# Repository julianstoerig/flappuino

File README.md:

# flappuino
tiny flappy bird for arduino w/OLED

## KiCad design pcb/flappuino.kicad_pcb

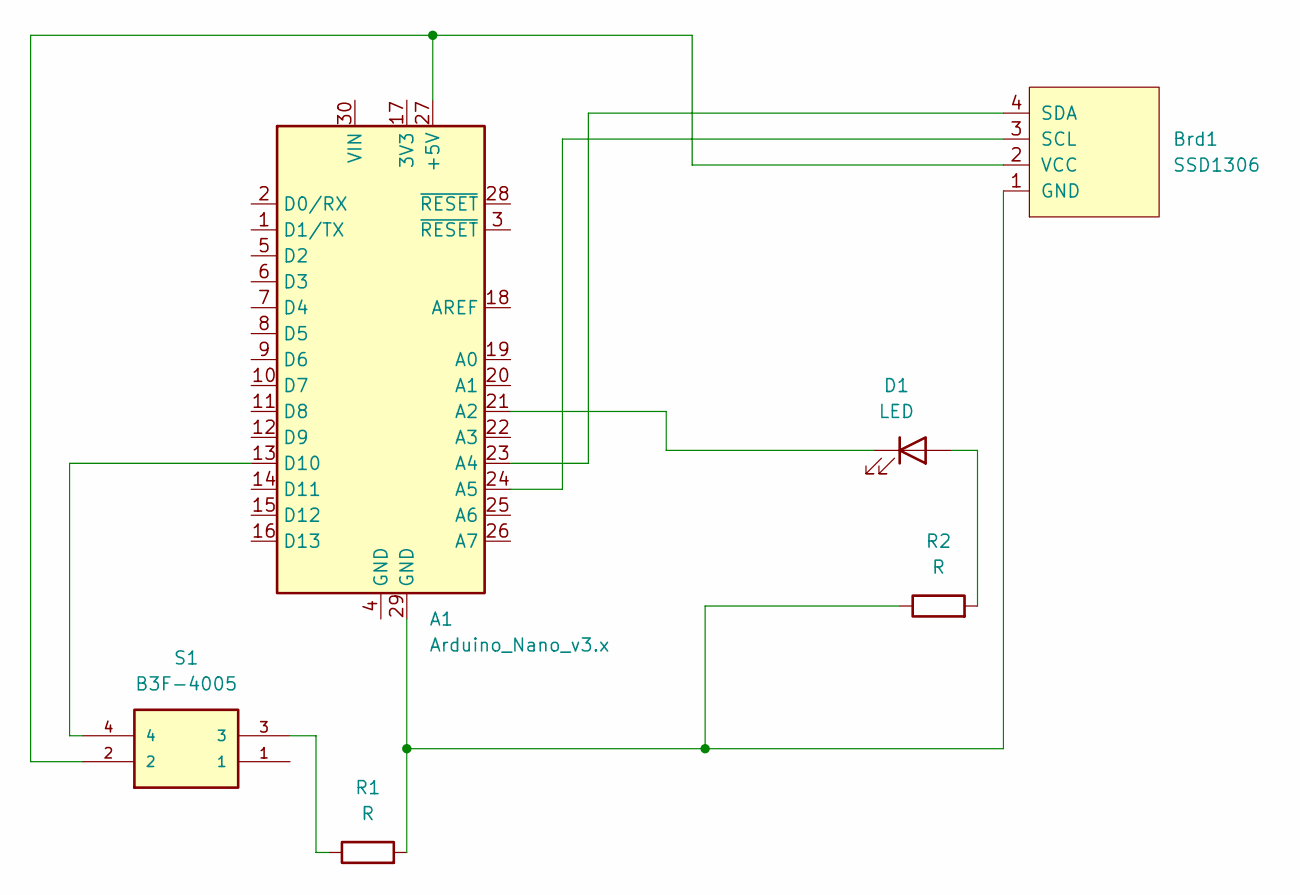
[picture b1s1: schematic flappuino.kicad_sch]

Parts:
A1: Arduino_Nano_v3.x; Arduino_Nano
Brd1: SSD1306; 128x64OLED
D1: LED; LED Universal Thruhole
R1, R2: R; Resistor Universal Thruhole
S1: B3F-4005; B3F-4055; Mouser_Part_Number 653-B3F-4005

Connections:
unnamed: A1.27 (+5V), Brd1.2 (VCC), S1.2
unnamed: A1.21 (A2), D1.1 (K)
unnamed: A1.23 (A4), Brd1.4 (SDA)
unnamed: A1.24 (A5), Brd1.3 (SCL)
unnamed: A1.13 (D10), S1.4
unnamed: A1.29 (GND), Brd1.1 (GND), R1.2, R2.1
unnamed: D1.2 (A), R2.2
unnamed: R1.1, S1.3

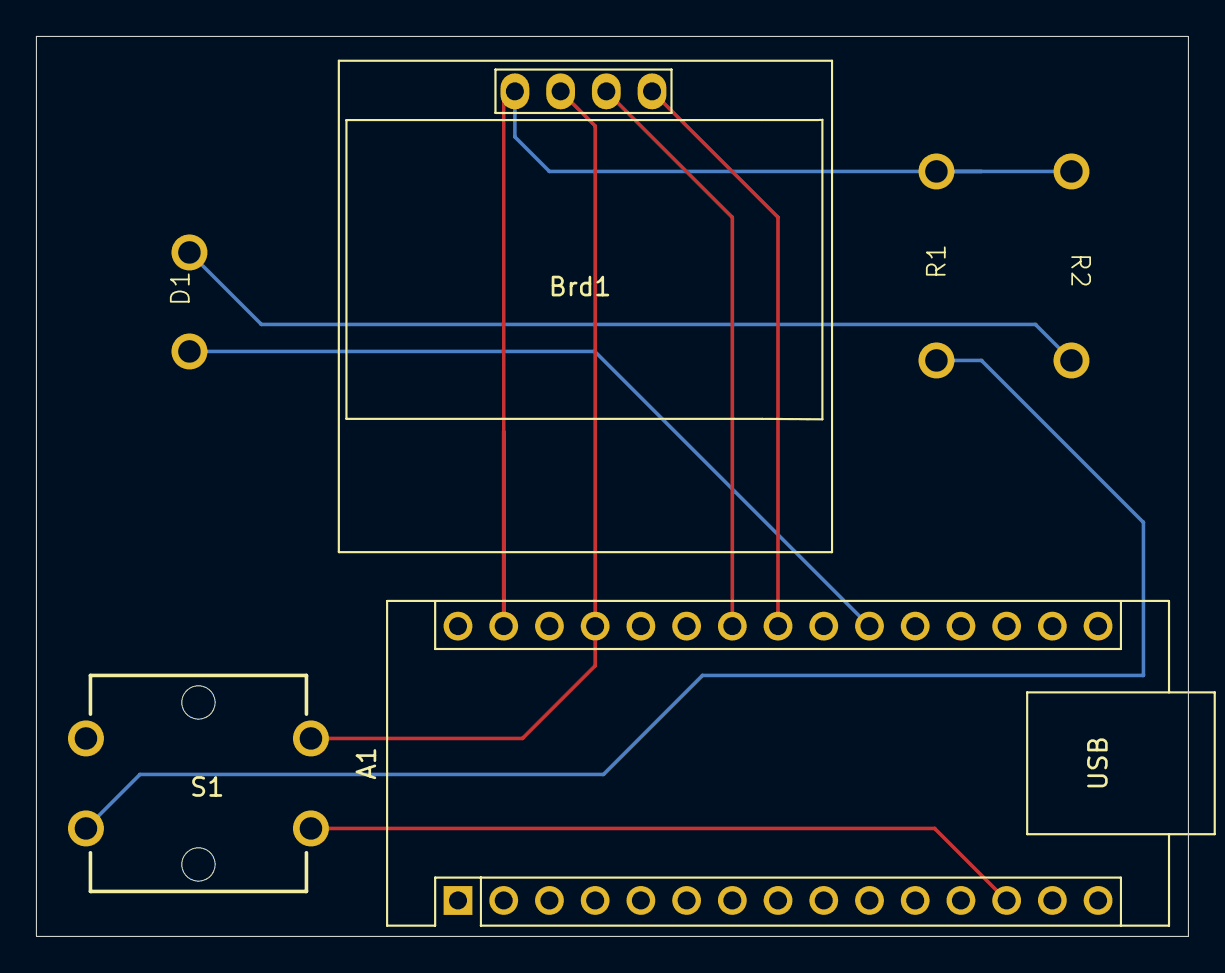
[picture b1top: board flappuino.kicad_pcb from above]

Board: 2 copper layers, 64.0 x 50.0 mm, 6 parts (0 on the bottom side), 8 nets.

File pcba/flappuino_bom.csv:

Designator,Footprint,Quantity,Value,LCSC Part #
A1,Arduino_Nano,1,Arduino_Nano_v3.x,
BRD1,128x64OLED,1,SSD1306,
D1,LED Universal Thruhole,1,LED,
"R1, R2",Resistor Universal Thruhole,2,R,
S1,B3F-4055,1,B3F-4005,

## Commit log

2025-11-11 adjust doc comments
2025-11-11 finalise ssd1306 init proc
2025-11-11 stuff
2025-11-11 remove text for size reasons
2025-11-11 next
2025-11-13 add error reporting
2025-11-13 remove unused file
2025-11-13 double speed
2025-11-14 Initial pcb (do not use)
    this is not tested but should work
2025-11-14 preview pcb
    this is just to preview the pcb inside github
2025-11-14 move pcb preview stl inside folder
